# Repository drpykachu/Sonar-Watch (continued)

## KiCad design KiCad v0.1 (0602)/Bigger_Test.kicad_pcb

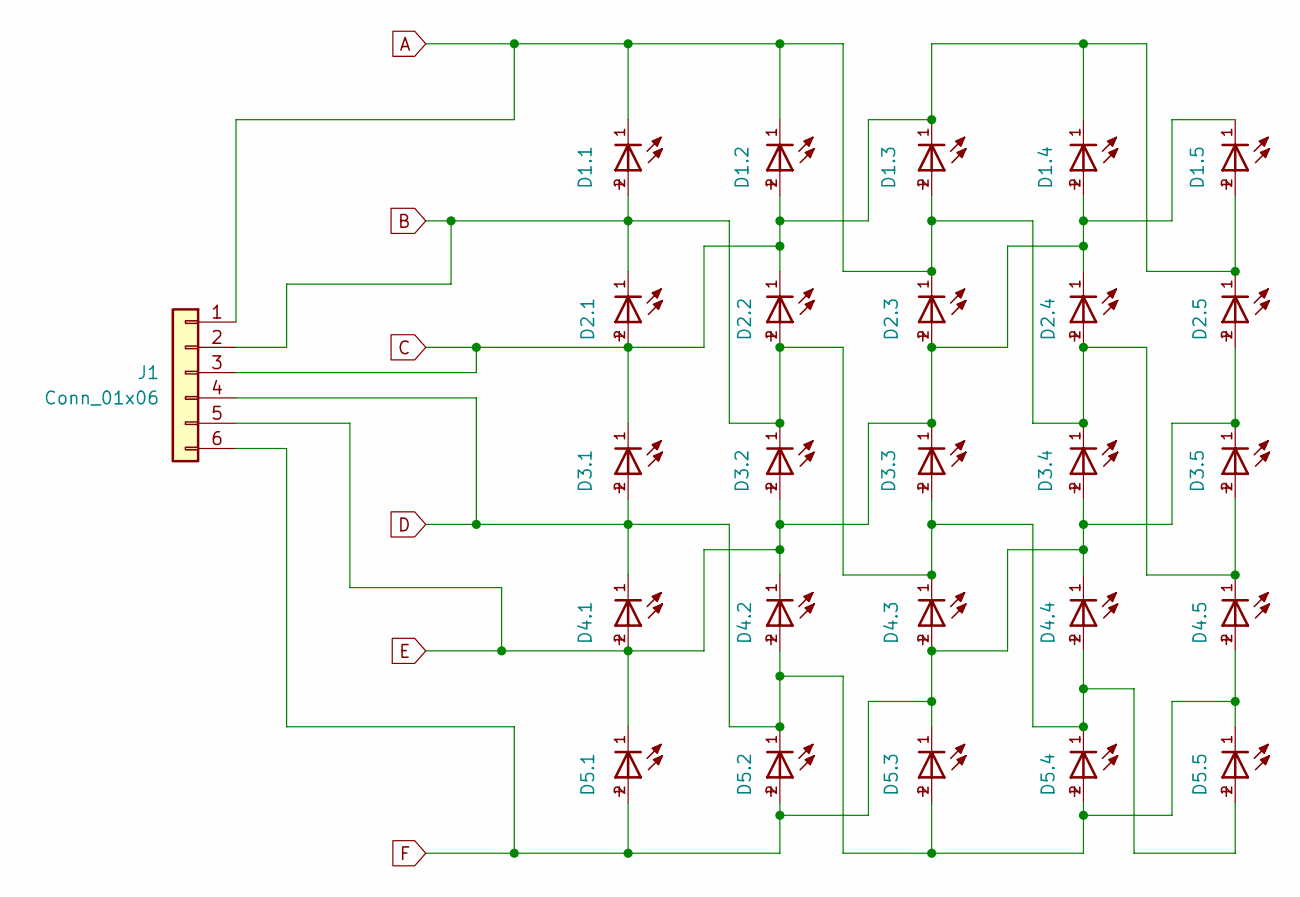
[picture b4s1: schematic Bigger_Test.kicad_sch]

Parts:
D1.1, D1.2, D1.3, D1.4, D1.5, D2.1, D2.2, D2.3, D2.4, D2.5, D3.1, D3.2, D3.3, D3.4, D3.5, D4.1, D4.2, D4.3, D4.4, D4.5, D5.1, D5.2, D5.3, D5.4, D5.5: WL-SMCW_0603
J1: Conn_01x06

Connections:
A: D1.1.1, D1.2.1, D1.3.2, D2.3.1, D2.4.2, D3.4.1, D3.5.2, D4.5.1, J1.1
B: D1.1.2, D2.1.1, D2.2.2, D3.2.1, D3.3.2, D4.3.1, D4.4.2, D5.4.1, D5.5.2, J1.2
C: D1.2.2, D1.3.1, D1.4.1, D1.5.2, D2.1.2, D2.2.1, D2.5.1, D3.1.1, J1.3
D: D3.1.2, D4.1.1, D4.2.2, D4.5.2, D5.2.1, D5.3.2, D5.4.2, D5.5.1, J1.4
E: D1.4.2, D1.5.1, D2.3.2, D2.4.1, D3.2.2, D3.3.1, D4.1.2, D4.2.1, D5.1.1, J1.5
F: D2.5.2, D3.4.2, D3.5.1, D4.3.2, D4.4.1, D5.1.2, D5.2.2, D5.3.1, J1.6

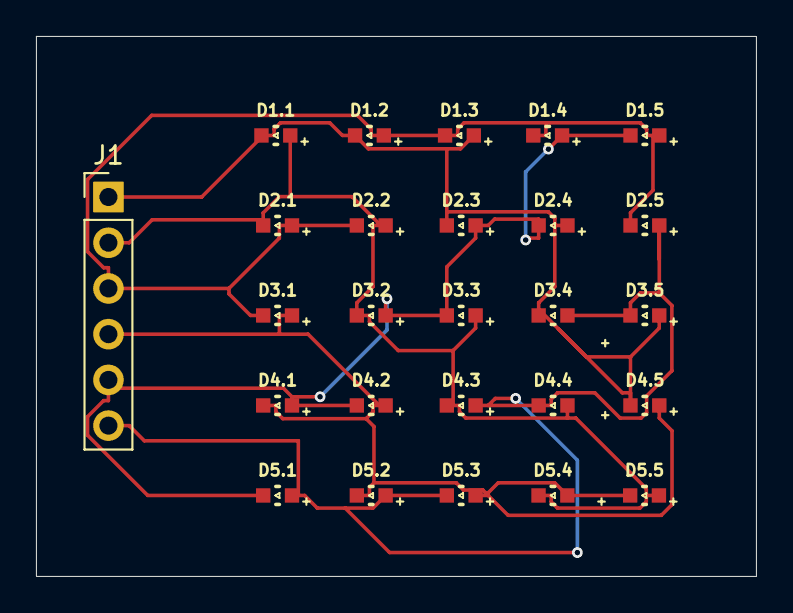
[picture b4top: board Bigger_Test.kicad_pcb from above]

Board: 2 copper layers, 40.0 x 30.0 mm, 26 parts (0 on the bottom side), 6 nets.

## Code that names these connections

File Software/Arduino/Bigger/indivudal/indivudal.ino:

const int pins[6] = {PA8, PF1, PF0, PB6, PA15, PB7};  // D9 to D4


const char* Charlie[5][5][6] = {
  {{"LOW", "HIGH", "INPUT", "INPUT", "INPUT", "INPUT"},     // 1.1
   {"LOW", "INPUT", "HIGH", "INPUT", "INPUT", "INPUT"},     // 1.2
   {"HIGH", "INPUT", "LOW", "INPUT", "INPUT", "INPUT"},     // 1.3
   {"INPUT", "INPUT", "LOW", "INPUT", "HIGH", "INPUT"},     // 1.4
   {"INPUT", "INPUT", "HIGH", "INPUT", "LOW", "INPUT"}},    // 1.5

  {{"INPUT", "LOW", "HIGH", "INPUT", "INPUT", "INPUT"},     // 2.1
   {"INPUT", "HIGH", "LOW", "INPUT", "INPUT", "INPUT"},     // 2.2
   {"LOW", "INPUT", "INPUT", "INPUT", "HIGH", "INPUT"},     // 2.3
   {"HIGH", "INPUT", "INPUT", "INPUT", "LOW", "INPUT"},     // 2.4
   {"INPUT", "INPUT", "LOW", "INPUT", "INPUT", "HIGH"}},    // 2.5

  {{"INPUT", "INPUT", "LOW", "HIGH", "INPUT", "INPUT"},     // 3.1
   {"INPUT", "LOW", "INPUT", "INPUT", "HIGH", "INPUT"},     // 3.2
   {"INPUT", "HIGH", "INPUT", "INPUT", "LOW", "INPUT"},     // 3.3
   {"LOW", "INPUT", "INPUT", "INPUT", "INPUT", "HIGH"},     // 3.4
   {"HIGH", "INPUT", "INPUT", "INPUT", "INPUT", "LOW"}},    // 3.5

  {{"INPUT", "INPUT", "INPUT", "LOW", "HIGH", "INPUT"},     // 4.1
   {"INPUT", "INPUT", "INPUT", "HIGH", "LOW", "INPUT"},     // 4.2
   {"INPUT", "LOW", "INPUT", "INPUT", "INPUT", "HIGH"},     // 4.3
   {"INPUT", "HIGH", "INPUT", "INPUT", "INPUT", "LOW"},     // 4.4
   {"LOW", "INPUT", "INPUT", "HIGH", "INPUT", "INPUT"}},    // 4.5

  {{"INPUT", "INPUT", "INPUT", "INPUT", "LOW", "HIGH"},     // 5.1
   {"INPUT", "INPUT", "INPUT", "LOW", "INPUT", "HIGH"},     // 5.2
   {"INPUT", "INPUT", "INPUT", "HIGH", "INPUT", "LOW"},     // 5.3
   {"INPUT", "LOW", "INPUT", "HIGH", "INPUT", "INPUT"},     // 5.4
   {"INPUT", "HIGH", "INPUT", "LOW", "INPUT", "INPUT"}}     // 5.5
};

int row = 0; // LOW
int col = 4; // HIGH

void setup() {
  Serial.begin(9600);
  PinReset();
}

void loop() {
  const char** netRow = Charlie[row][col];

  for (int i = 0; i < 6; i++) {
    int pin = pins[i];
    const char* mode = netRow[i];

    if (strcmp(mode, "LOW") == 0) {
      pinMode(pin, OUTPUT);
      digitalWrite(pin, LOW);
    } else if (strcmp(mode, "HIGH") == 0) {
      pinMode(pin, OUTPUT);
      digitalWrite(pin, HIGH);
    } else {
      pinMode(pin, INPUT);
    }
  }

  delayMicroseconds(150);
  PinReset();
  // delay(10);
}

void PinReset() {
  for (int i = 0; i < 6; i++) {
    pinMode(pins[i], INPUT);
  }
}

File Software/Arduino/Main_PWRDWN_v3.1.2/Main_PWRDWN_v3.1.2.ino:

#include <avr/sleep.h>
#include <avr/interrupt.h>
#include <avr/wdt.h>
#include "RTClib.h"
#include "WatchData.h"
#include "WatchFunc.h"
#include <string.h>

// === Flags ===
volatile bool wake_flag = false;
volatile bool CHG_flag = false;
volatile bool wdt_flag = false;  // <-- New flag for watchdog wake

// === Pins ===
const int SCL_PIN = 3;
const int Bat_ON = 21;
const int Button = 22;  // PF2 (pin 2 on Arduino pinout — confirm on your board)
const int RTC_WAKE = 23;
const int Charge_STAT = 14;
const int Bat_READ = A11;  // 25
const int SDA_PIN = 32;

// === RTC ===
RTC_DS3231 rtc;
DateTime now;

// === Settings ===
int hour = 1;
int minute = 1;
int second = 1;
bool options_mode = false;
bool options_section = true;
int clock_mode = 0;
int wrist_mode = 0;
int LED_flip = 0;
int brightness = 50;
int charge = 1;
unsigned long fade_duration = 1000;
unsigned long charge_timer = 1000;

unsigned long battery_ticks = 0;          // Counts watchdog cycles (~8s each)
const unsigned long batteryTarget = 450;  // 450×8s ≈ 1 hour

int NaN = -1;
int life_start = true;
int press_count = 0;

void setup() {
  rtc.begin();
  rtc.adjust(DateTime(F(__DATE__), F(__TIME__)));

  pinMode(Bat_READ, INPUT);
  pinMode(RTC_WAKE, OUTPUT);
  digitalWrite(RTC_WAKE, HIGH);

  pinMode(Bat_ON, OUTPUT);
  digitalWrite(Bat_ON, HIGH);

  // --- Button interrupt setup (rising edge) ---
  pinMode(Button, INPUT_PULLUP);        // Button connected to PF2 with pullup
  PORTF.PIN2CTRL = PORT_ISC_RISING_gc;  // Enable interrupt on rising edge
  PORTF.INTFLAGS = PIN2_bm;             // Clear any pending interrupt

  // --- Charger interrupt (falling edge) ---
  pinMode(Charge_STAT, INPUT_PULLUP);
  PORTD.PIN2CTRL = PORT_ISC_FALLING_gc;
  PORTD.INTFLAGS = PIN2_bm;

  // --- Sleep setup ---
  SLPCTRL.CTRLA = SLPCTRL_SMODE_PDOWN_gc | SLPCTRL_SEN_bm;

  // --- Watchdog setup (8s interval) ---
  _PROTECTED_WRITE(WDT.CTRLA, 0);  // Disable first, safe change
  _PROTECTED_WRITE(WDT.CTRLA,
                   WDT_PERIOD_8KCLK_gc |  // 8-second period
                                          //  WDT_ENABLE_bm         | // Enable WDT
                     WDT_WINDOW_OFF_gc);  // Disable window mode
  WDT.STATUS = 0;                         // Clear sync busy flag (safety)
  // WDT.INTCTRL = WDT_INTMODE_bm;  // Enable interrupt mode

  sei();  // Enable global interrupts
}

void loop() {

  // --- Wake from watchdog (~8s cycle) ---
  if (wdt_flag) {
    wdt_flag = false;
    battery_ticks++;
    if (battery_ticks >= batteryTarget) {  // ~1 hour elapsed
      battery_ticks = 0;
      charge = analogRead(Bat_READ);
      float voltage = charge * (3.0 / 1023.0);  // assuming 3.3V reference
      if (voltage <= 2.0) {
        digitalWrite(Bat_ON, LOW);
      }
    }
  }

  // --- Wake from charger ---
  if (CHG_flag) {
    CHG_flag = false;
    CHG_flash(2);
    wake_flag = false;
  }

  // --- Wake from button ---
  if (wake_flag) {
    wake_flag = false;

    pinMode(RTC_WAKE, LOW);  // Power up DS3231
    delay(50);
    now = rtc.now();
    hour = now.hour();
    minute = now.minute();
    pinMode(RTC_WAKE, HIGH);  // Power down DS3231

    if (hour >= 12) hour -= 12;

    if (clock_mode == 0) {
      Ring_Execute(hour, minute);
    } else {
      Clock_Execute(hour, minute);
    }
  }

  options_mode = Hold_Timer(1000);
  if (options_mode == true) {

    All_flash(0.05, 100, 3);

    //////////// Battery module
    if (options_mode = true) {
      press_count = -1;
      Mod_Battery();
      options_section = true;
    }
    //////////// Brightness module
    if (options_mode = true) {
      Mod_Brightness();
      options_section = true;
    }
    //////////// Hour module
    if (options_mode = true) {
      Mod_Hour();
      options_section = true;
    }
    //////////// Minute Module
    if (options_mode = true) {
      Mod_Minute();
      options_section = true;
    }
    ////////// Clocktype Module
    if (options_mode = true) {
      Mod_ClockMode();
      options_section = true;
    }

    ////////// Wristtype Module
    if (options_mode = true) {
      Mod_WristMode();
      options_section = true;
    }

    ////////////// Closes Modules
    options_mode = false;
    All_flash(0.05, 100, 3);

    Crab_Timer(2000);

    delay(50);
  }


 
  // --- Enter power-down ---
  __asm__ __volatile__("sleep");
}

// === Button Interrupt (PF2) ===
ISR(PORTF_PORT_vect) {
  if (!(VPORTF.IN & (1 << 2))) return;  // Only act on rising edge
  PORTF.INTFLAGS = PIN2_bm;             // Clear interrupt flag
  wake_flag = true;
}

// === Charger Interrupt (PD2) ===
ISR(PORTD_PORT_vect) {
  if (VPORTD.IN & (1 << 2)) return;  // Only act on falling edge
  PORTD.INTFLAGS = PIN2_bm;
  CHG_flag = true;
}

// === Watchdog Interrupt ===
ISR(WDT_vect) {
  wdt_flag = true;  // Set flag so loop() can handle it
}

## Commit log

2025-05-06 Initial File Dump
2025-05-14 Major Udpate 2
2025-05-27 v0.3 sent for fab, v0.4 still in progress
    v0.3 and v0.4 have the same component footprints - that way, I only need to have 1 stencil (if v0.3 works!!!)
2025-06-12 STM32 Chip update
    For some reason, for which I don't know, it is impossible to use tri state logic consistently with the STM32G431KBT6. There is, im guessing, parasitic capacitance between Port A and Port B pins that 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
2025-06-30 Complete v0.1 update
    So I learned a lot of things!
    1.) Micro vias and blind vias add a lot of additional manufacturing costs. Avoid them at all costs
    2.) RTC modules can be used with I2C, so I opted for the DS3231
    3.) The use of the UPDI is awesome - so I used an ATMEGA4808 chip. The grounds need to be common, but the Vsup does not! Tested, and works. Means one less trace/connection of the board (and one less 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
    4.) PCBWAY requires a minimum pad clearance of 0.22mm for black solder masks. Had to learn how to make custom design rules in KiCad.
    5.) There's more, but those are the biggest this udpate.
2025-08-06 Complete v2.0 update
    Skipped over the v1.0 update as the v1.0 was board is the exact same as the v2.0 board, except for one footprint change.
    1.) I have found an inconsistency in one of the footprints and models located on Digikey pertaining to ATMEGA4808-AF. The Ultra Librarian model and footprint do not match the 32TQFP footprint represe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
    2.) After reviewing the Atmega4808 datasheet, I now know that no all pins have the functionality to wake the microcontroller from deep sleep mode. Idle mode allows for all pins to wake up the device 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
2025-08-06 Housekeeping
2025-08-08 Software v1.0 update
    - Added two clock modes:
    • PING: a sonar ping unveils the hour (inner dot) and minute (outer dot)
    • 4DIG: just 4 digits (HHMM) displaying time.
    - Added a charge indicator when the magnetic charger is plugged in
    - Added all the options modules:
    • Battery life indicator
2025-08-11 Software v1.1 Update
    - Made a python GUI to easily create LED patterns on watch using buttons. Easy for copy/paste into Arduino
    - Crab
2025-08-11 Software v1.1 Update
    Software v1.1 Update
    - Made a python GUI to easily create LED patterns on watch using buttons. Easy for copy/paste into Arduino
    - Crab
2025-09-28 Update - V3.0
    I lied. I said I was going to stop working on hardware and only focus on software. But something was bothering me. The two mistakes in version 2.0 were: one of the pins was always high (no idea) and 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
2025-09-30 Version 3 software update
    • set the BOD to 2.6V (dont go higher than that)
    • Added charger wake flag
    • Added charger indicator
    • Set the software version number to match the hardware number
2025-10-05 Version 3 - Software update
    - Added increased battery protection (with watchdog timer)
    - Added John Conway's Game of Life as an easter egg
2025-10-05 reupdate (forgot some code)
2025-10-15 Trying to add battery saver module
    work in progress
2025-11-09 Near Final Update
    Found out the BOD controller only shuts down the chip control instead of shutting down the functionality of the pins. I have rewrote the software to use a different control function (VLM instead of B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
    Additionally, I re-wired 2 traces on the circuit board so that the battery-percentage module is 100% safe and will not drain the battery. It's not worth paying the money to get new boards printed, si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
    This needs to be tested, of course.
2026-01-01 Last Update - Part 1
    Well, this project is coming to an end. I have found a way to safely shut down the watch - by checking the battery voltage by intervals of seconds * previous battery percentage. That way, 99% will ha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
2026-01-03 Final code tweeks
2026-01-14 initial update :)
